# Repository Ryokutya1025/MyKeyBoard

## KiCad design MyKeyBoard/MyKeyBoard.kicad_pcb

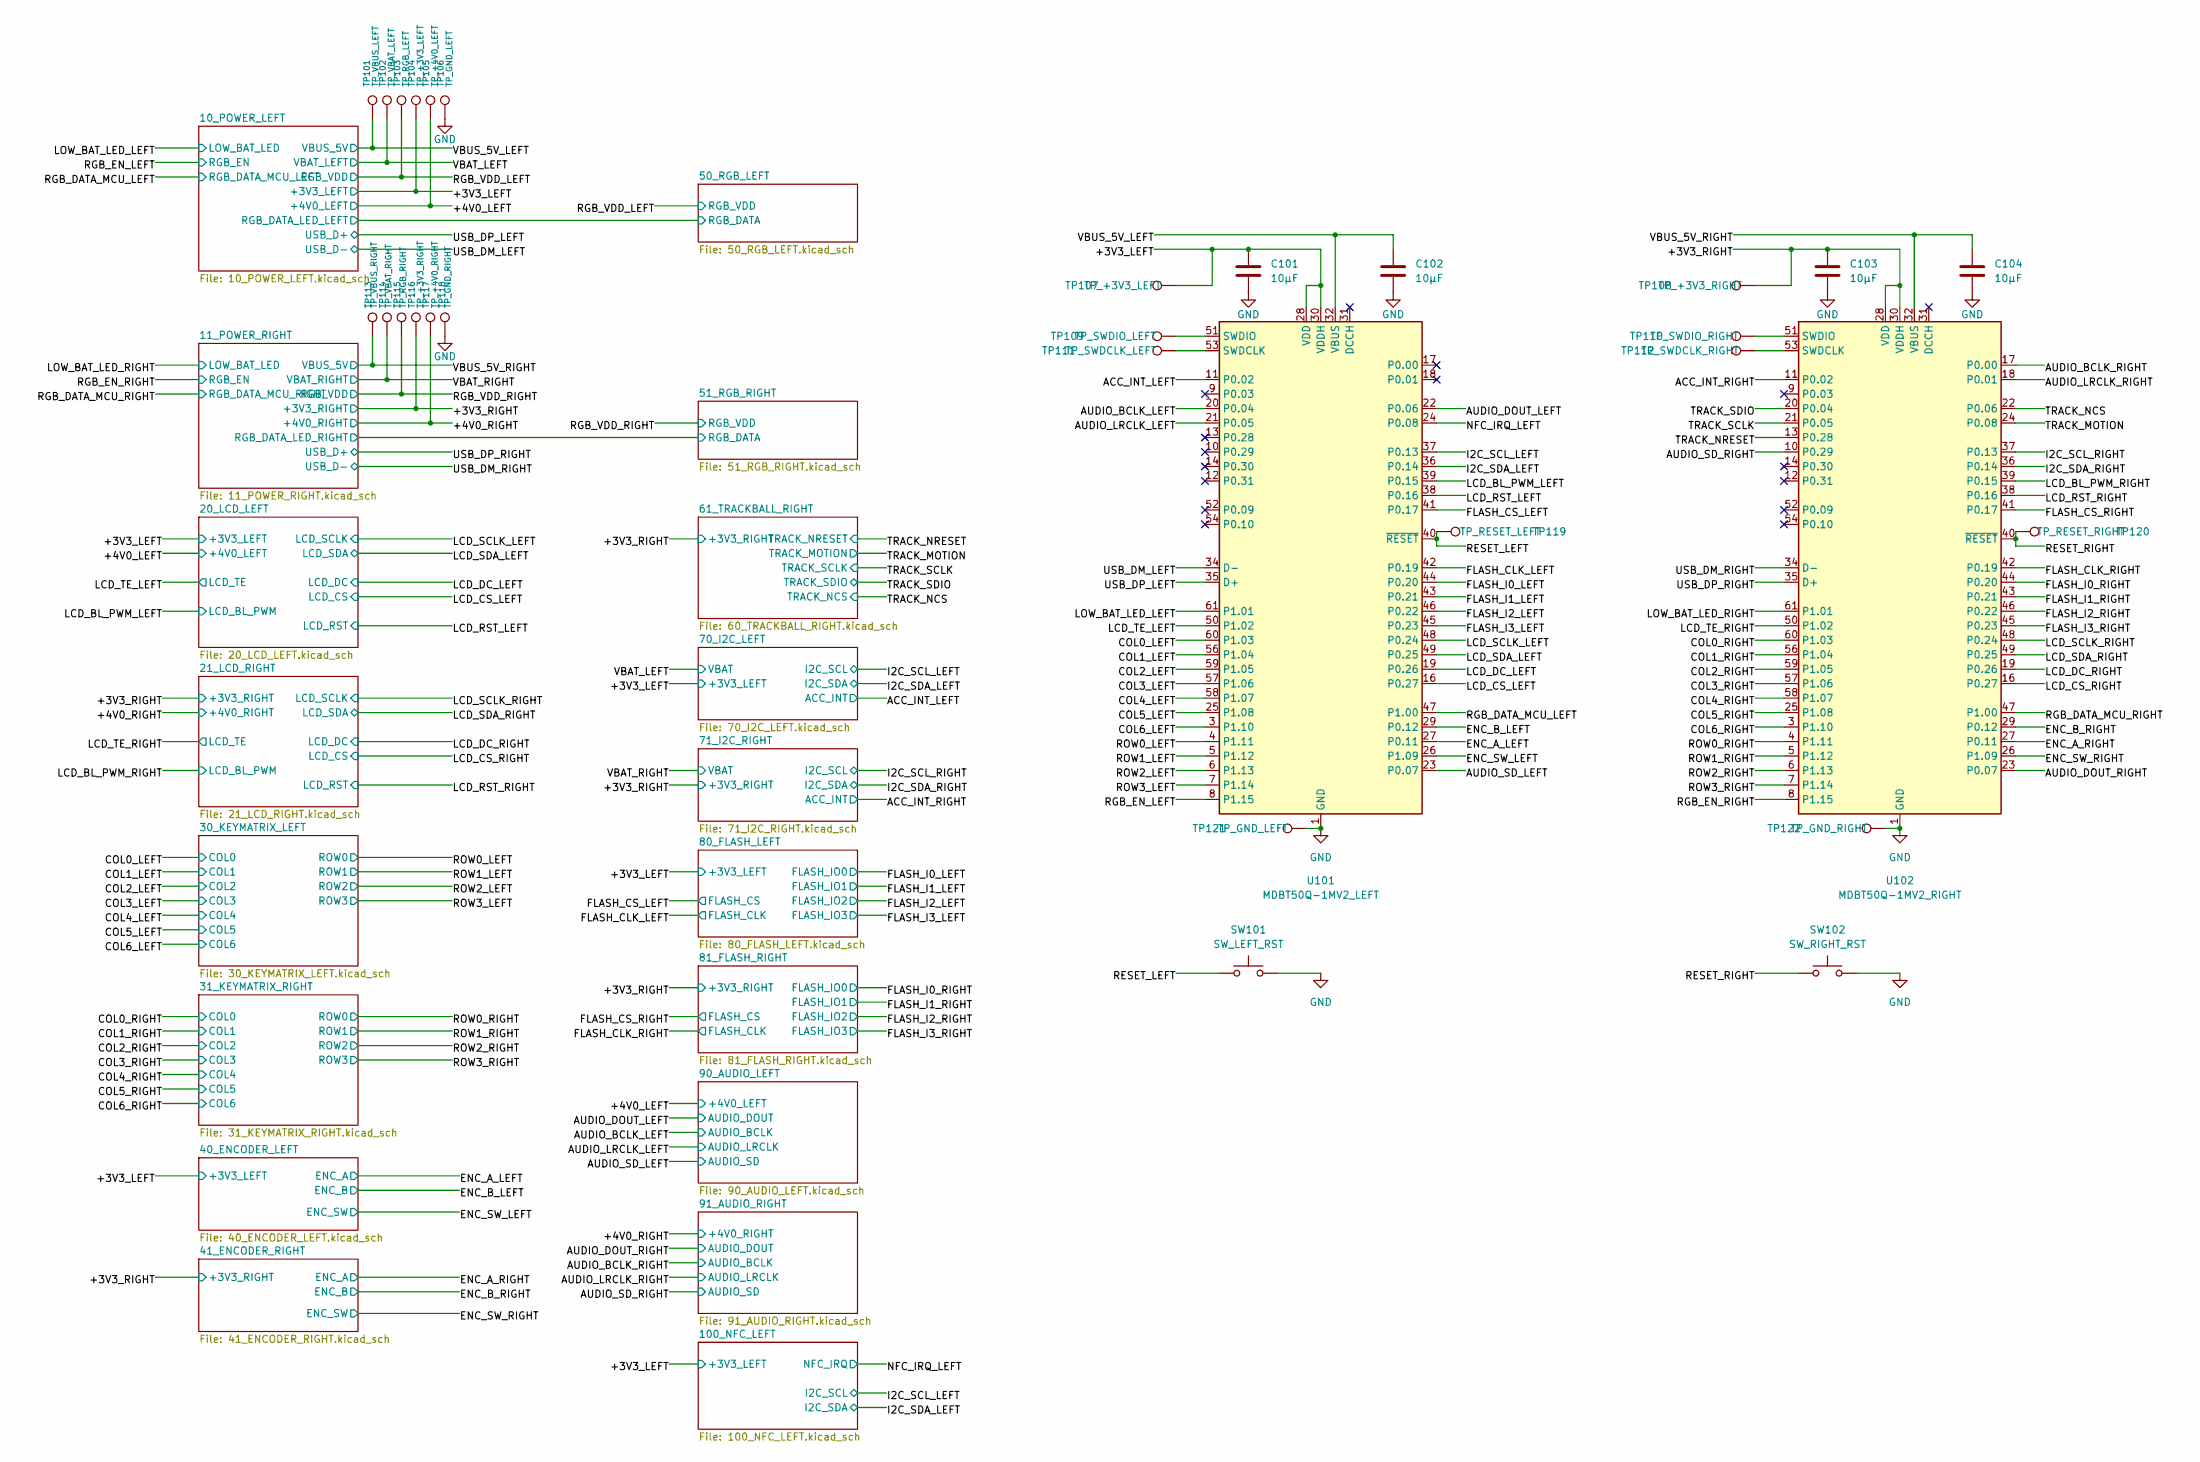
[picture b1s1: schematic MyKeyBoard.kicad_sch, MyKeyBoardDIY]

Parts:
C101, C102, C103, C104: 10µF; C_0805_2012Metric
SW101: SW_LEFT_RST; SW_SPST_B3U-1000P
SW102: SW_RIGHT_RST; SW_SPST_B3U-1000P
TP101: TP_VBUS_LEFT; TestPoint_Pad_D1.5mm
TP102: TP_VBAT_LEFT; TestPoint_Pad_D1.5mm
TP103: TP_RGB_LEFT; TestPoint_Pad_D1.5mm
TP104, TP107: TP_+3V3_LEFT; TestPoint_Pad_D1.5mm
TP105: TP_+4V0_LEFT; TestPoint_Pad_D1.5mm
TP106, TP121: TP_GND_LEFT; TestPoint_Pad_D1.5mm
TP108, TP116: TP_+3V3_RIGHT; TestPoint_Pad_D1.5mm
TP109: TP_SWDIO_LEFT; TestPoint_Pad_D1.5mm
TP110: TP_SWDIO_RIGHT; TestPoint_Pad_D1.5mm
TP111: TP_SWDCLK_LEFT; TestPoint_Pad_D1.5mm
TP112: TP_SWDCLK_RIGHT; TestPoint_Pad_D1.5mm
TP113: TP_VBUS_RIGHT; TestPoint_Pad_D1.5mm
TP114: TP_VBAT_RIGHT; TestPoint_Pad_D1.5mm
TP115: TP_RGB_RIGHT; TestPoint_Pad_D1.5mm
TP117: TP_+4V0_RIGHT; TestPoint_Pad_D1.5mm
TP118, TP122: TP_GND_RIGHT; TestPoint_Pad_D1.5mm
TP119: TP_RESET_LEFT; TestPoint_Pad_D1.5mm
TP120: TP_RESET_RIGHT; TestPoint_Pad_D1.5mm
U101: MDBT50Q-1MV2_LEFT; Raytac_MDBT50Q
U102: MDBT50Q-1MV2_RIGHT; Raytac_MDBT50Q

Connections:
/+3V3_LEFT: C101.2, TP104.1 (1_1), TP107.1 (1_1), U101.28 (VDD), U101.30 (VDDH); also elsewhere on the board
/+3V3_RIGHT: C103.1, TP108.1 (1_1), TP116.1 (1_1), U102.28 (VDD), U102.30 (VDDH); also elsewhere on the board
/+4V0_LEFT: TP105.1 (1_1); also elsewhere on the board
/+4V0_RIGHT: TP117.1 (1_1); also elsewhere on the board
/ACC_INT_LEFT: U101.11 (P0.02); also elsewhere on the board
/ACC_INT_RIGHT: U102.11 (P0.02); also elsewhere on the board
/AUDIO_BCLK_LEFT: U101.20 (P0.04); also elsewhere on the board
/AUDIO_BCLK_RIGHT: U102.17 (P0.00); also elsewhere on the board
/AUDIO_DOUT_LEFT: U101.22 (P0.06); also elsewhere on the board
/AUDIO_DOUT_RIGHT: U102.23 (P0.07); also elsewhere on the board
/AUDIO_LRCLK_LEFT: U101.21 (P0.05); also elsewhere on the board
/AUDIO_LRCLK_RIGHT: U102.18 (P0.01); also elsewhere on the board
/AUDIO_SD_LEFT: U101.23 (P0.07); also elsewhere on the board
/AUDIO_SD_RIGHT: U102.10 (P0.29); also elsewhere on the board
/COL0_LEFT: U101.60 (P1.03); also elsewhere on the board
/COL0_RIGHT: U102.60 (P1.03); also elsewhere on the board
/COL1_LEFT: U101.56 (P1.04); also elsewhere on the board
/COL1_RIGHT: U102.56 (P1.04); also elsewhere on the board
/COL2_LEFT: U101.59 (P1.05); also elsewhere on the board
/COL2_RIGHT: U102.59 (P1.05); also elsewhere on the board
/COL3_LEFT: U101.57 (P1.06); also elsewhere on the board
/COL3_RIGHT: U102.57 (P1.06); also elsewhere on the board
/COL4_LEFT: U101.58 (P1.07); also elsewhere on the board
/COL4_RIGHT: U102.58 (P1.07); also elsewhere on the board
/COL5_LEFT: U101.25 (P1.08); also elsewhere on the board
/COL5_RIGHT: U102.25 (P1.08); also elsewhere on the board
/COL6_LEFT: U101.3 (P1.10); also elsewhere on the board
/COL6_RIGHT: U102.3 (P1.10); also elsewhere on the board
/ENC_A_LEFT: U101.27 (P0.11); also elsewhere on the board
/ENC_A_RIGHT: U102.27 (P0.11); also elsewhere on the board
/ENC_B_LEFT: U101.29 (P0.12); also elsewhere on the board
/ENC_B_RIGHT: U102.29 (P0.12); also elsewhere on the board
/ENC_SW_LEFT: U101.26 (P1.09); also elsewhere on the board
/ENC_SW_RIGHT: U102.26 (P1.09); also elsewhere on the board
/FLASH_CLK_LEFT: U101.42 (P0.19); also elsewhere on the board
/FLASH_CLK_RIGHT: U102.42 (P0.19); also elsewhere on the board
/FLASH_CS_LEFT: U101.41 (P0.17); also elsewhere on the board
/FLASH_CS_RIGHT: U102.41 (P0.17); also elsewhere on the board
/FLASH_I0_LEFT: U101.44 (P0.20); also elsewhere on the board
/FLASH_I0_RIGHT: U102.44 (P0.20); also elsewhere on the board
/FLASH_I1_LEFT: U101.43 (P0.21); also elsewhere on the board
/FLASH_I1_RIGHT: U102.43 (P0.21); also elsewhere on the board
/FLASH_I2_LEFT: U101.46 (P0.22); also elsewhere on the board
/FLASH_I2_RIGHT: U102.46 (P0.22); also elsewhere on the board
/FLASH_I3_LEFT: U101.45 (P0.23); also elsewhere on the board
/FLASH_I3_RIGHT: U102.45 (P0.23); also elsewhere on the board
/I2C_SCL_LEFT: U101.37 (P0.13); also elsewhere on the board
/I2C_SCL_RIGHT: U102.37 (P0.13); also elsewhere on the board
/I2C_SDA_LEFT: U101.36 (P0.14); also elsewhere on the board
/I2C_SDA_RIGHT: U102.36 (P0.14); also elsewhere on the board
/LCD_BL_PWM_LEFT: U101.39 (P0.15); also elsewhere on the board
/LCD_BL_PWM_RIGHT: U102.39 (P0.15); also elsewhere on the board
/LCD_CS_LEFT: U101.16 (P0.27); also elsewhere on the board
/LCD_CS_RIGHT: U102.16 (P0.27); also elsewhere on the board
/LCD_DC_LEFT: U101.19 (P0.26); also elsewhere on the board
/LCD_DC_RIGHT: U102.19 (P0.26); also elsewhere on the board
/LCD_RST_LEFT: U101.38 (P0.16); also elsewhere on the board
/LCD_RST_RIGHT: U102.38 (P0.16); also elsewhere on the board
/LCD_SCLK_LEFT: U101.48 (P0.24); also elsewhere on the board
/LCD_SCLK_RIGHT: U102.48 (P0.24); also elsewhere on the board
/LCD_SDA_LEFT: U101.49 (P0.25); also elsewhere on the board
/LCD_SDA_RIGHT: U102.49 (P0.25); also elsewhere on the board
/LCD_TE_LEFT: U101.50 (P1.02); also elsewhere on the board
/LCD_TE_RIGHT: U102.50 (P1.02); also elsewhere on the board
/LOW_BAT_LED_LEFT: U101.61 (P1.01); also elsewhere on the board
/LOW_BAT_LED_RIGHT: U102.61 (P1.01); also elsewhere on the board
/NFC_IRQ_LEFT: U101.24 (P0.08); also elsewhere on the board
/RESET_LEFT: SW101.1, TP119.1 (1_1), U101.40 (~RESET)
/RESET_RIGHT: SW102.1, TP120.1 (1_1), U102.40 (~RESET)
/RGB_DATA_MCU_LEFT: U101.47 (P1.00); also elsewhere on the board
/RGB_DATA_MCU_RIGHT: U102.47 (P1.00); also elsewhere on the board
/RGB_EN_LEFT: U101.8 (P1.15); also elsewhere on the board
/RGB_EN_RIGHT: U102.8 (P1.15); also elsewhere on the board
/RGB_VDD_LEFT: TP103.1 (1_1); also elsewhere on the board
/RGB_VDD_RIGHT: TP115.1 (1_1); also elsewhere on the board
/ROW0_LEFT: U101.4 (P1.11); also elsewhere on the board
/ROW0_RIGHT: U102.4 (P1.11); also elsewhere on the board
/ROW1_LEFT: U101.5 (P1.12); also elsewhere on the board
/ROW1_RIGHT: U102.5 (P1.12); also elsewhere on the board
/ROW2_LEFT: U101.6 (P1.13); also elsewhere on the board
/ROW2_RIGHT: U102.6 (P1.13); also elsewhere on the board
/ROW3_LEFT: U101.7 (P1.14); also elsewhere on the board
/ROW3_RIGHT: U102.7 (P1.14); also elsewhere on the board
/TRACK_MOTION: U102.24 (P0.08); also elsewhere on the board
/TRACK_NCS: U102.22 (P0.06); also elsewhere on the board
/TRACK_NRESET: U102.13 (P0.28); also elsewhere on the board
/TRACK_SCLK: U102.21 (P0.05); also elsewhere on the board
/TRACK_SDIO: U102.20 (P0.04); also elsewhere on the board
/USB_DM_LEFT: U101.34 (D-); also elsewhere on the board
/USB_DM_RIGHT: U102.34 (D-); also elsewhere on the board
/USB_DP_LEFT: U101.35 (D+); also elsewhere on the board
/USB_DP_RIGHT: U102.35 (D+); also elsewhere on the board
/VBAT_LEFT: TP102.1 (1_1); also elsewhere on the board
/VBAT_RIGHT: TP114.1 (1_1); also elsewhere on the board
/VBUS_5V_LEFT: C102.2, TP101.1 (1_1), U101.32 (VBUS); also elsewhere on the board
/VBUS_5V_RIGHT: C104.1, TP113.1 (1_1), U102.32 (VBUS); also elsewhere on the board
GND: C101.1, C102.1, C103.2, C104.2, SW101.2, SW102.2, TP106.1 (1_1), TP118.1 (1_1), TP121.1 (1_1), TP122.1 (1_1), U101.1 (GND), U101.2 (GND), U101.15 (GND), U101.33 (GND), U101.55 (GND), U102.1 (GND), U102.2 (GND), U102.15 (GND), U102.33 (GND), U102.55 (GND); also elsewhere on the board
unnamed: TP111.1 (1_1), U101.53 (SWDCLK)
unnamed: TP109.1 (1_1), U101.51 (SWDIO)
unnamed: TP112.1 (1_1), U102.53 (SWDCLK)
unnamed: TP110.1 (1_1), U102.51 (SWDIO)

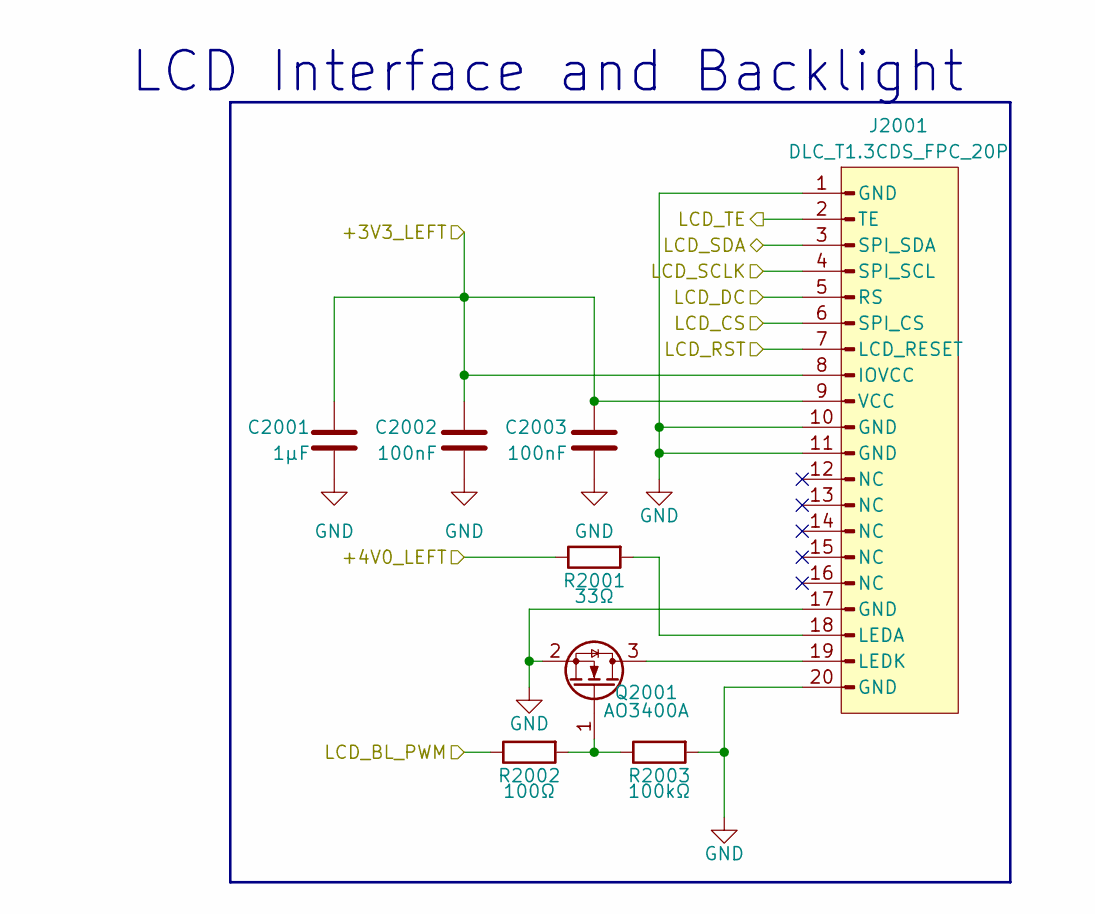
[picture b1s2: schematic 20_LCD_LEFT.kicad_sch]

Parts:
C2001: 1µF; C_0603_1608Metric
C2002, C2003: 100nF; C_0603_1608Metric
J2001: DLC_T1.3CDS_FPC_20P
Q2001: AO3400A; SOT-23
R2001: 33Ω; R_0603_1608Metric
R2002: 100Ω; R_0603_1608Metric
R2003: 100kΩ; R_0603_1608Metric

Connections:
/+3V3_LEFT: C2001.1, C2002.1, C2003.1, J2001.8 (IOVCC), J2001.9 (VCC); also elsewhere on the board
/+4V0_LEFT: R2001.1; also elsewhere on the board
/LCD_BL_PWM_LEFT: R2002.1; also elsewhere on the board
/LCD_CS_LEFT: J2001.6 (SPI_CS); also elsewhere on the board
/LCD_DC_LEFT: J2001.5 (RS); also elsewhere on the board
/LCD_RST_LEFT: J2001.7 (LCD_RESET); also elsewhere on the board
/LCD_SCLK_LEFT: J2001.4 (SPI_SCL); also elsewhere on the board
/LCD_SDA_LEFT: J2001.3 (SPI_SDA); also elsewhere on the board
/LCD_TE_LEFT: J2001.2 (TE); also elsewhere on the board
GND: C2001.2, C2002.2, C2003.2, J2001.1 (GND), J2001.10 (GND), J2001.11 (GND), J2001.17 (GND), J2001.20 (GND), Q2001.2 (S), R2003.2; also elsewhere on the board
unnamed: J2001.18 (LEDA), R2001.2
unnamed: J2001.19 (LEDK), Q2001.3 (D)
unnamed: Q2001.1 (G), R2002.2, R2003.1

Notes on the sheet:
LCD Interface and Backlight

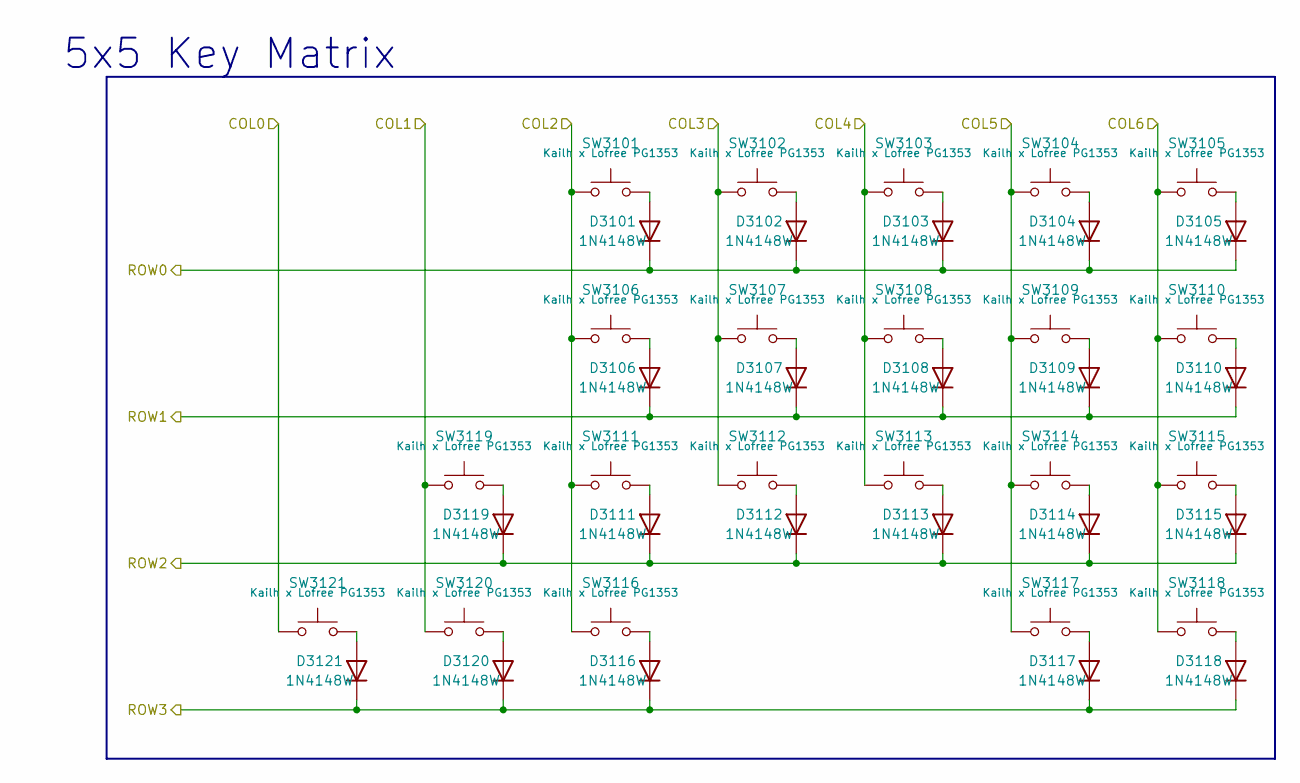
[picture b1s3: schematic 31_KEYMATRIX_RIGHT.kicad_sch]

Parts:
D3101, D3102, D3103, D3104, D3105, D3106, D3107, D3108, D3109, D3110, D3111, D3112, D3113, D3114, D3115, D3116, D3117, D3118, D3119, D3120, D3121: 1N4148W; D_SOD-123
SW3101, SW3102, SW3103, SW3104, SW3105, SW3106, SW3107, SW3108, SW3109, SW3110, SW3111, SW3112, SW3113, SW3114, SW3115, SW3116, SW3117, SW3118, SW3119, SW3120, SW3121: Kailh x Lofree PG1353; Kailh-PG1353-Hotswap-1U

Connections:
/COL0_RIGHT: SW3121.1; also elsewhere on the board
/COL1_RIGHT: SW3119.1, SW3120.1; also elsewhere on the board
/COL2_RIGHT: SW3101.1, SW3106.1, SW3111.1, SW3116.1; also elsewhere on the board
/COL3_RIGHT: SW3102.1, SW3107.1, SW3112.1; also elsewhere on the board
/COL4_RIGHT: SW3103.1, SW3108.1, SW3113.1; also elsewhere on the board
/COL5_RIGHT: SW3104.1, SW3109.1, SW3114.1, SW3117.1; also elsewhere on the board
/COL6_RIGHT: SW3105.1, SW3110.1, SW3115.1, SW3118.1; also elsewhere on the board
/ROW0_RIGHT: D3101.1 (K), D3102.1 (K), D3103.1 (K), D3104.1 (K), D3105.1 (K); also elsewhere on the board
/ROW1_RIGHT: D3106.1 (K), D3107.1 (K), D3108.1 (K), D3109.1 (K), D3110.1 (K); also elsewhere on the board
/ROW2_RIGHT: D3111.1 (K), D3112.1 (K), D3113.1 (K), D3114.1 (K), D3115.1 (K), D3119.1 (K); also elsewhere on the board
/ROW3_RIGHT: D3116.1 (K), D3117.1 (K), D3118.1 (K), D3120.1 (K), D3121.1 (K); also elsewhere on the board
unnamed: D3101.2 (A), SW3101.2
unnamed: D3102.2 (A), SW3102.2
unnamed: D3103.2 (A), SW3103.2
unnamed: D3104.2 (A), SW3104.2
unnamed: D3105.2 (A), SW3105.2
unnamed: D3106.2 (A), SW3106.2
unnamed: D3107.2 (A), SW3107.2
unnamed: D3108.2 (A), SW3108.2
unnamed: D3109.2 (A), SW3109.2
unnamed: D3110.2 (A), SW3110.2
unnamed: D3111.2 (A), SW3111.2
unnamed: D3112.2 (A), SW3112.2
unnamed: D3113.2 (A), SW3113.2
unnamed: D3114.2 (A), SW3114.2
unnamed: D3115.2 (A), SW3115.2
unnamed: D3116.2 (A), SW3116.2
unnamed: D3117.2 (A), SW3117.2
unnamed: D3118.2 (A), SW3118.2
unnamed: D3119.2 (A), SW3119.2
unnamed: D3120.2 (A), SW3120.2
unnamed: D3121.2 (A), SW3121.2

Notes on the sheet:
5x5 Key Matrix

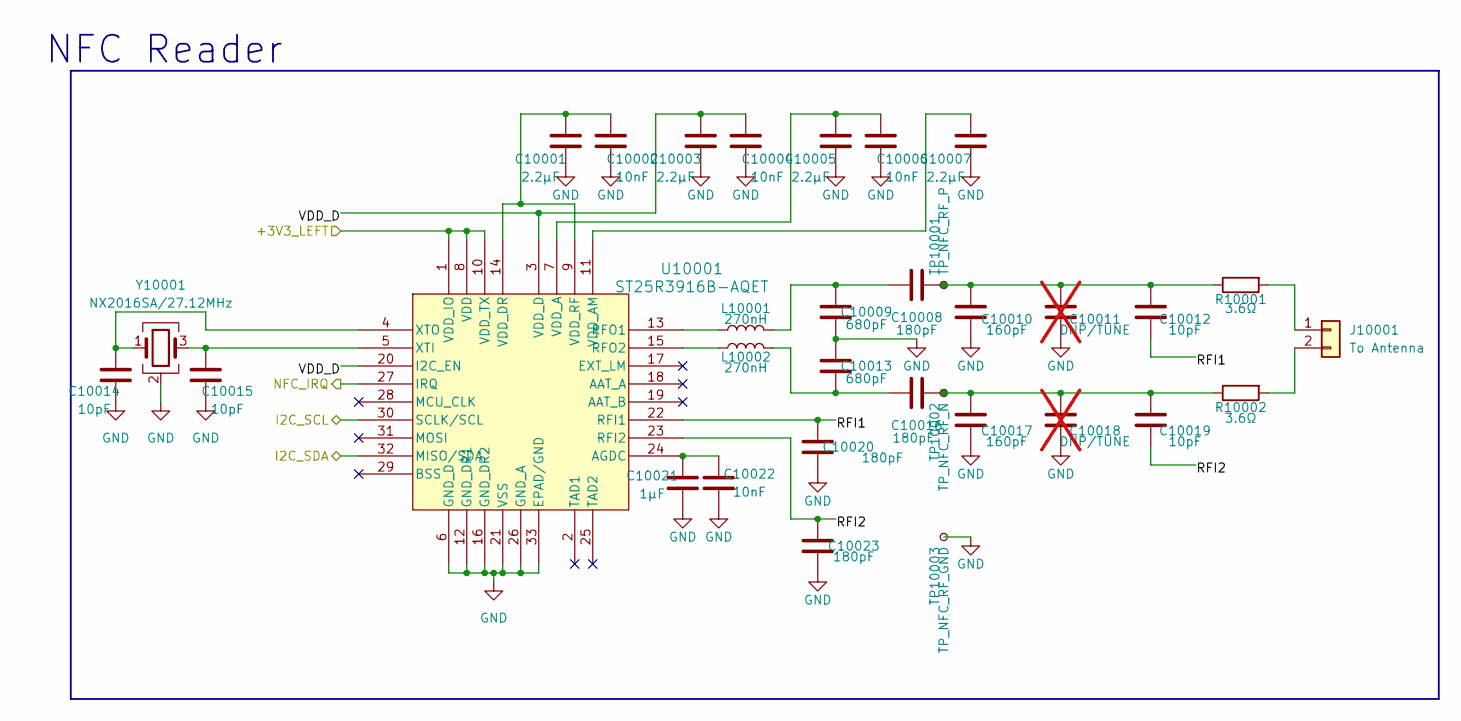
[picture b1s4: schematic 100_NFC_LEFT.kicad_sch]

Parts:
C10001, C10003, C10005, C10007: 2.2µF; C_0805_2012Metric
C10002, C10004, C10006, C10022: 10nF; C_0603_1608Metric
C10008, C10016, C10020, C10023: 180pF; C_0603_1608Metric
C10009, C10013: 680pF; C_0603_1608Metric
C10010, C10017: 160pF; C_0603_1608Metric
C10011, C10018: DNP/TUNE; C_0603_1608Metric; not fitted
C10012, C10014, C10015, C10019: 10pF; C_0603_1608Metric
C10021: 1µF; C_0603_1608Metric
J10001: To Antenna; JST_SH_SM02B-SRSS-TB_1x02-1MP_P1.00mm_Horizontal
L10001, L10002: 270nH; L_0603_1608Metric
R10001, R10002: 3.6Ω; R_0603_1608Metric
TP10001: TP_NFC_RF_P; TestPoint_Pad_D1.0mm
TP10002: TP_NFC_RF_N; TestPoint_Pad_D1.0mm
TP10003: TP_NFC_RF_GND; TestPoint_Pad_D1.5mm
U10001: ST25R3916B-AQET; UFQFPN32-5x5x0p55_STM
Y10001: NX2016SA/27.12MHz; Crystal_SMD_2016-4Pin_2.0x1.6mm

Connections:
/100_NFC_LEFT/RFI1: C10012.1, C10020.1, U10001.22 (RFI1)
/100_NFC_LEFT/RFI2: C10019.1, C10023.1, U10001.23 (RFI2)
/100_NFC_LEFT/VDD_D: C10003.1, C10004.1, U10001.3 (VDD_D), U10001.20 (I2C_EN)
/+3V3_LEFT: U10001.1 (VDD_IO), U10001.8 (VDD), U10001.10 (VDD_TX); also elsewhere on the board
/I2C_SCL_LEFT: U10001.30 (SCLK/SCL); also elsewhere on the board
/I2C_SDA_LEFT: U10001.32 (MISO/SDA); also elsewhere on the board
/NFC_IRQ_LEFT: U10001.27 (IRQ); also elsewhere on the board
GND: C10001.2, C10002.2, C10003.2, C10004.2, C10005.2, C10006.2, C10007.2, C10009.2, C10010.1, C10011.1, C10013.1, C10014.2, C10015.2, C10017.1, C10018.1, C10020.2, C10021.2, C10022.2, C10023.2, TP10003.1 (1_1), U10001.6 (GND_D), U10001.12 (GND_DR1), U10001.16 (GND_DR2), U10001.21 (VSS), U10001.26 (GND_A), U10001.33 (EPAD/GND), Y10001.2 (G), Y10001.4 (G); also elsewhere on the board
unnamed: C10008.1, C10009.1, L10001.2
unnamed: C10008.2, C10010.2, C10011.2, C10012.2, R10001.1, TP10001.1 (1_1)
unnamed: C10013.2, C10016.1, L10002.1
unnamed: C10016.2, C10017.2, C10018.2, C10019.2, R10002.1, TP10002.1 (1_1)
unnamed: J10001.1, R10001.2
unnamed: J10001.2, R10002.2
unnamed: C10021.1, C10022.1, U10001.24 (AGDC)
unnamed: L10001.1, U10001.13 (RFO1)
unnamed: L10002.2, U10001.15 (RFO2)
unnamed: C10005.1, C10006.1, U10001.7 (VDD_A)
unnamed: C10007.1, U10001.11 (VDD_AM)
unnamed: C10001.1, C10002.1, U10001.9 (VDD_RF), U10001.14 (VDD_DR)
unnamed: C10015.1, U10001.5 (XTI), Y10001.3
unnamed: C10014.1, U10001.4 (XTO), Y10001.1

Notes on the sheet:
NFC Reader

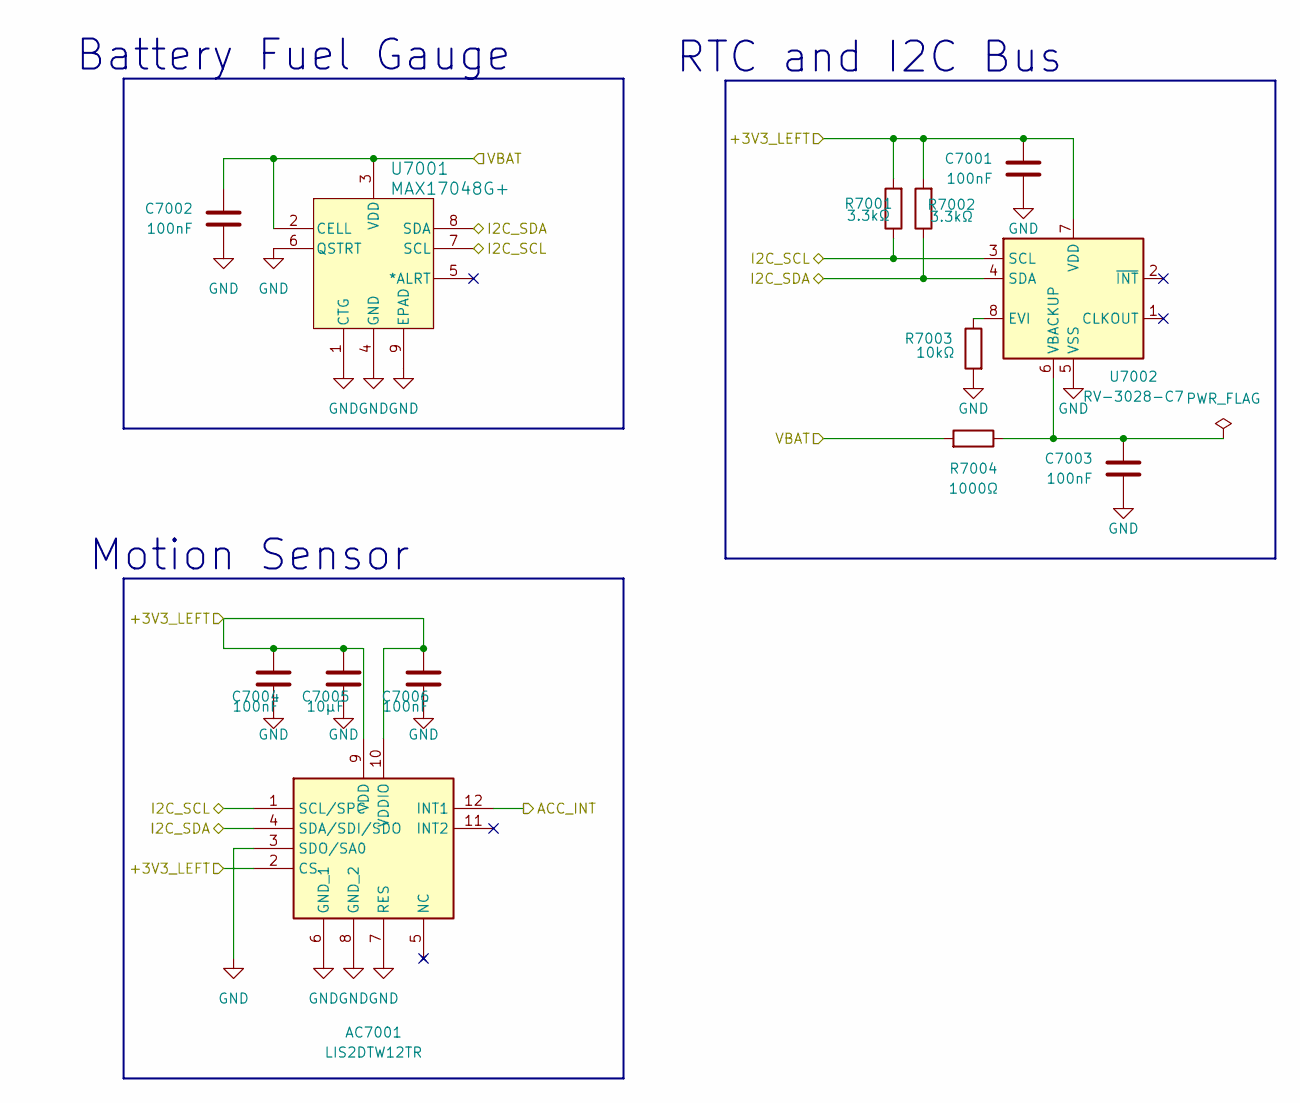
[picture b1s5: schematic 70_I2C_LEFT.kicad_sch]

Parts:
AC7001: LIS2DTW12TR; LGA-12_2x2mm_P0.5mm; Mouser Part Number 511-LIS2DTW12TR
C7001, C7002, C7003, C7004, C7006: 100nF; C_0603_1608Metric
C7005: 10µF; C_0805_2012Metric
R7001, R7002: 3.3kΩ; R_0603_1608Metric
R7003: 10kΩ; R_0603_1608Metric
R7004: 1000Ω; R_0603_1608Metric
U7001: MAX17048G+
U7002: RV-3028-C7

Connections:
/+3V3_LEFT: AC7001.2 (CS), AC7001.9 (VDD), AC7001.10 (VDDIO), C7001.1, C7004.1, C7005.1, C7006.1, R7001.2, R7002.2, U7002.7 (VDD); also elsewhere on the board
/ACC_INT_LEFT: AC7001.12 (INT1); also elsewhere on the board
/I2C_SCL_LEFT: AC7001.1 (SCL/SPC), R7001.1, U7001.7 (SCL), U7002.3 (SCL); also elsewhere on the board
/I2C_SDA_LEFT: AC7001.4 (SDA/SDI/SDO), R7002.1, U7001.8 (SDA), U7002.4 (SDA); also elsewhere on the board
/VBAT_LEFT: C7002.1, R7004.2, U7001.2 (CELL), U7001.3 (VDD); also elsewhere on the board
GND: AC7001.3 (SDO/SA0), AC7001.6 (GND_1), AC7001.7 (RES), AC7001.8 (GND_2), C7001.2, C7002.2, C7003.2, C7004.2, C7005.2, C7006.2, R7003.2, U7001.1 (CTG), U7001.4 (GND), U7001.6 (QSTRT), U7001.9 (EPAD), U7002.5 (VSS); also elsewhere on the board
unnamed: R7003.1, U7002.8 (EVI)
unnamed: C7003.1, R7004.1, U7002.6 (VBACKUP)

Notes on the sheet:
Battery Fuel Gauge
RTC and I2C Bus
Motion Sensor

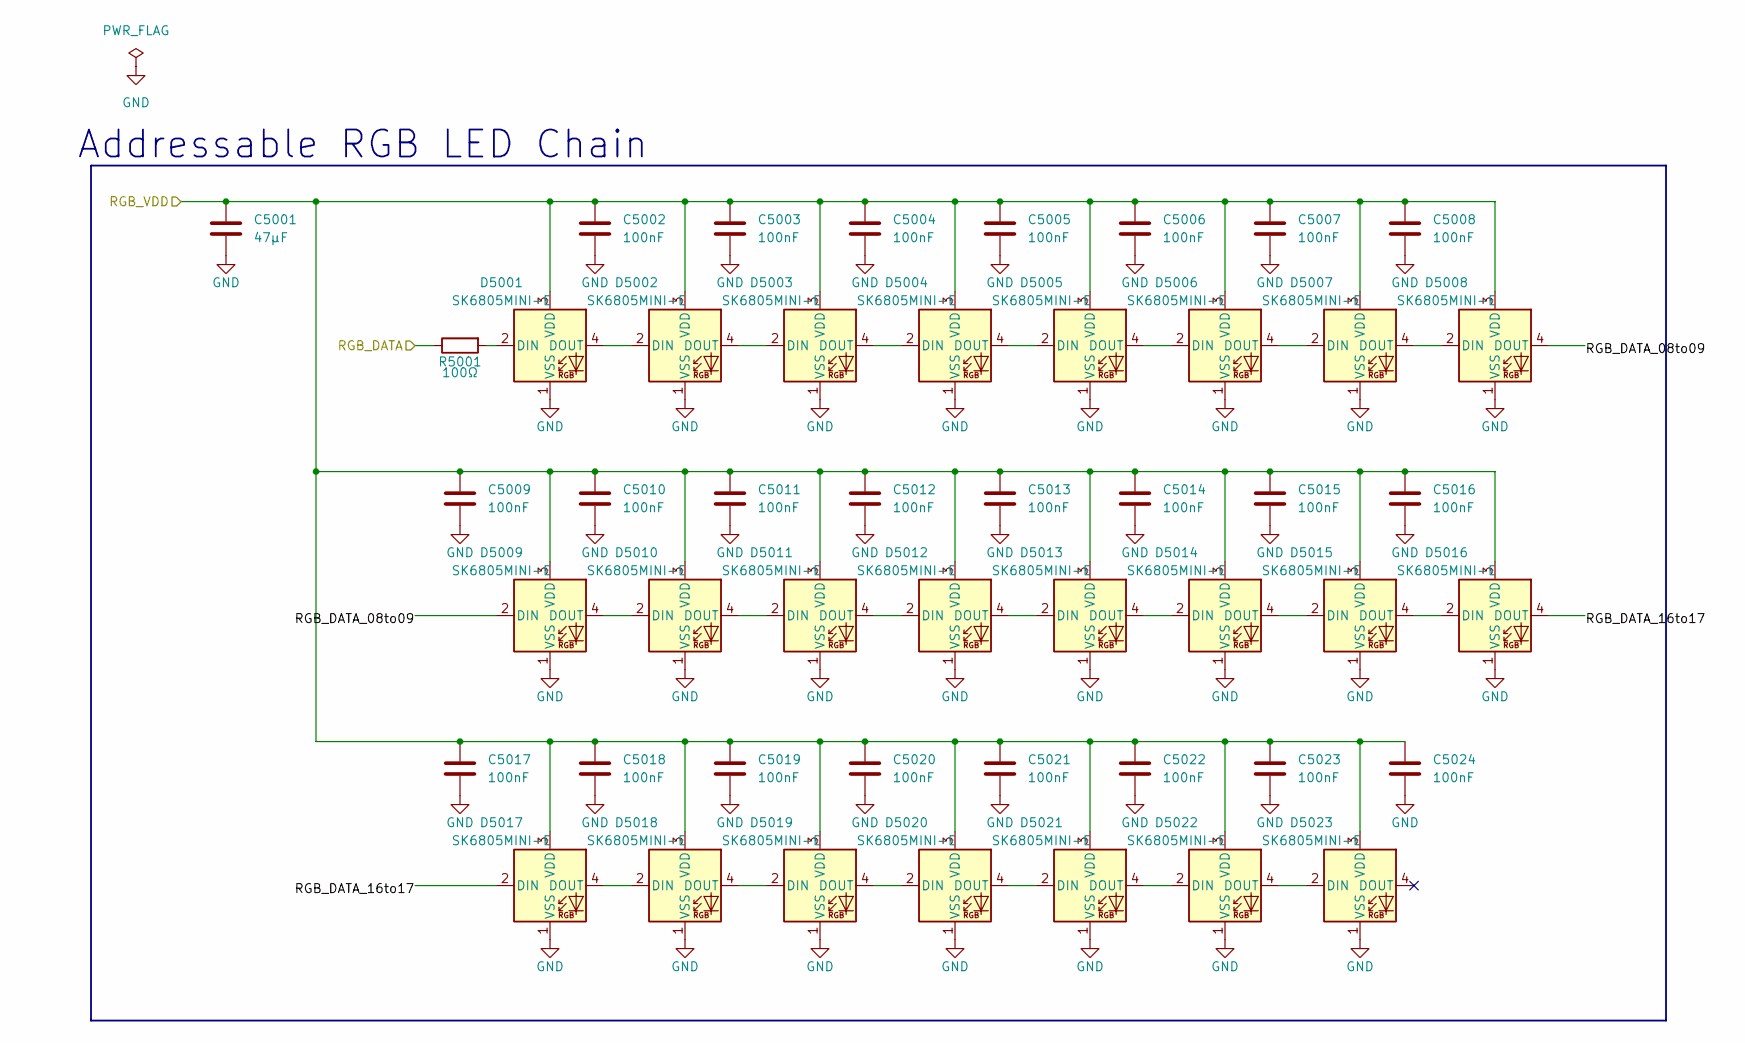
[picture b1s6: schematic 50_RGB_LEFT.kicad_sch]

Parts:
C5001: 47µF; C_1210_3225Metric
C5002, C5003, C5004, C5005, C5006, C5007, C5008, C5009, C5010, C5011, C5012, C5013, C5014, C5015, C5016, C5017, C5018, C5019, C5020, C5021, C5022, C5023, C5024: 100nF; C_0603_1608Metric
D5001, D5002, D5003, D5004, D5005, D5006, D5007, D5008, D5009, D5010, D5011, D5012, D5013, D5014, D5015, D5016, D5017, D5018, D5019, D5020, D5021, D5022, D5023: SK6805MINI-E
R5001: 100Ω; R_0603_1608Metric

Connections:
/10_POWER_LEFT/RGB_DATA_LED_LEFT: R5001.1; also elsewhere on the board
/50_RGB_LEFT/RGB_DATA_08to09: D5008.4 (DOUT), D5009.2 (DIN)
/50_RGB_LEFT/RGB_DATA_16to17: D5016.4 (DOUT), D5017.2 (DIN)
/RGB_VDD_LEFT: C5001.1, C5002.1, C5003.1, C5004.1, C5005.1, C5006.1, C5007.1, C5008.1, C5009.1, C5010.1, C5011.1, C5012.1, C5013.1, C5014.1, C5015.1, C5016.1, C5017.1, C5018.1, C5019.1, C5020.1, C5021.1, C5022.1, C5023.1, C5024.1, D5001.3 (VDD), D5002.3 (VDD), D5003.3 (VDD), D5004.3 (VDD), D5005.3 (VDD), D5006.3 (VDD), D5007.3 (VDD), D5008.3 (VDD), D5009.3 (VDD), D5010.3 (VDD), D5011.3 (VDD), D5012.3 (VDD), D5013.3 (VDD), D5014.3 (VDD), D5015.3 (VDD), D5016.3 (VDD), D5017.3 (VDD), D5018.3 (VDD), D5019.3 (VDD), D5020.3 (VDD), D5021.3 (VDD), D5022.3 (VDD), D5023.3 (VDD); also elsewhere on the board
GND: C5001.2, C5002.2, C5003.2, C5004.2, C5005.2, C5006.2, C5007.2, C5008.2, C5009.2, C5010.2, C5011.2, C5012.2, C5013.2, C5014.2, C5015.2, C5016.2, C5017.2, C5018.2, C5019.2, C5020.2, C5021.2, C5022.2, C5023.2, C5024.2, D5001.1 (VSS), D5002.1 (VSS), D5003.1 (VSS), D5004.1 (VSS), D5005.1 (VSS), D5006.1 (VSS), D5007.1 (VSS), D5008.1 (VSS), D5009.1 (VSS), D5010.1 (VSS), D5011.1 (VSS), D5012.1 (VSS), D5013.1 (VSS), D5014.1 (VSS), D5015.1 (VSS), D5016.1 (VSS), D5017.1 (VSS), D5018.1 (VSS), D5019.1 (VSS), D5020.1 (VSS), D5021.1 (VSS), D5022.1 (VSS), D5023.1 (VSS); also elsewhere on the board
unnamed: D5001.2 (DIN), R5001.2
unnamed: D5001.4 (DOUT), D5002.2 (DIN)
unnamed: D5002.4 (DOUT), D5003.2 (DIN)
unnamed: D5003.4 (DOUT), D5004.2 (DIN)
unnamed: D5004.4 (DOUT), D5005.2 (DIN)
unnamed: D5005.4 (DOUT), D5006.2 (DIN)
unnamed: D5006.4 (DOUT), D5007.2 (DIN)
unnamed: D5007.4 (DOUT), D5008.2 (DIN)
unnamed: D5009.4 (DOUT), D5010.2 (DIN)
unnamed: D5010.4 (DOUT), D5011.2 (DIN)
unnamed: D5011.4 (DOUT), D5012.2 (DIN)
unnamed: D5012.4 (DOUT), D5013.2 (DIN)
unnamed: D5013.4 (DOUT), D5014.2 (DIN)
unnamed: D5014.4 (DOUT), D5015.2 (DIN)
unnamed: D5015.4 (DOUT), D5016.2 (DIN)
unnamed: D5017.4 (DOUT), D5018.2 (DIN)
unnamed: D5018.4 (DOUT), D5019.2 (DIN)
unnamed: D5019.4 (DOUT), D5020.2 (DIN)
unnamed: D5020.4 (DOUT), D5021.2 (DIN)
unnamed: D5021.4 (DOUT), D5022.2 (DIN)
unnamed: D5022.4 (DOUT), D5023.2 (DIN)

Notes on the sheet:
Addressable RGB LED Chain

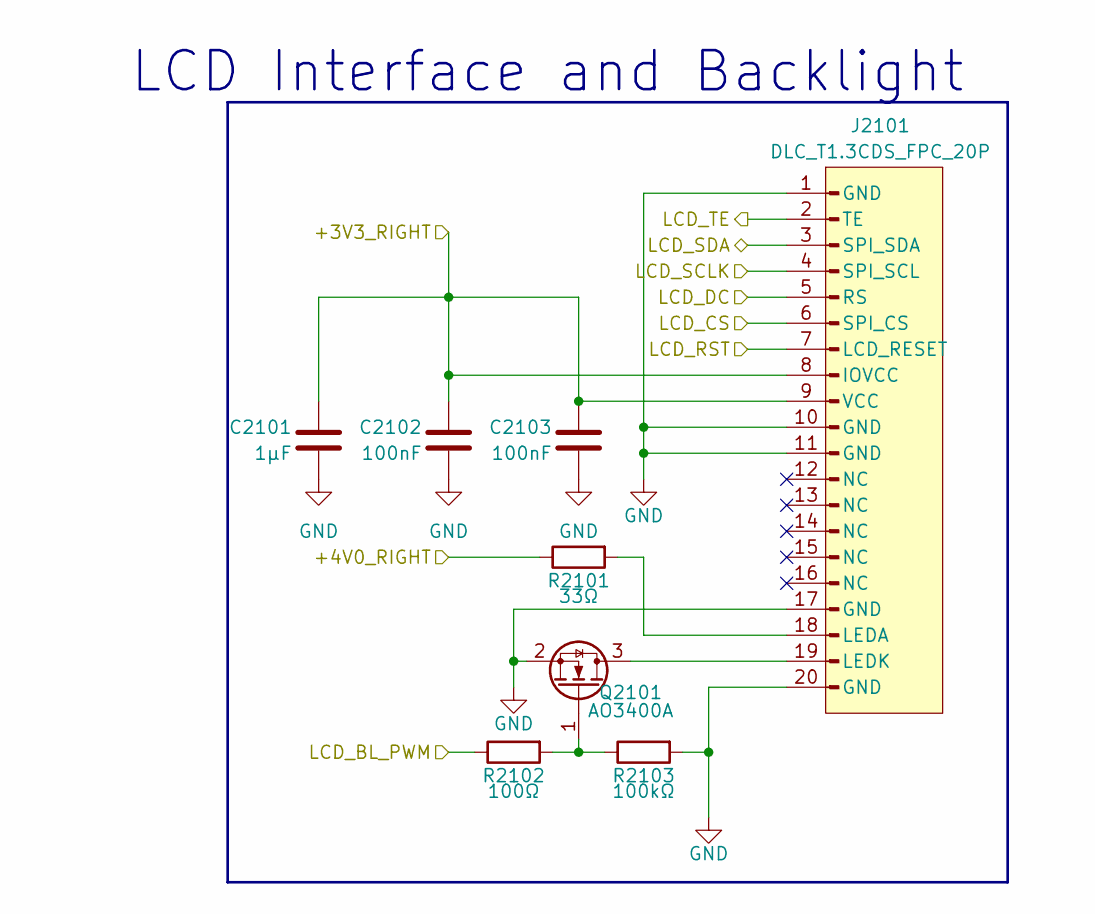
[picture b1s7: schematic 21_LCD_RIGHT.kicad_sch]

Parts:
C2101: 1µF; C_0603_1608Metric
C2102, C2103: 100nF; C_0603_1608Metric
J2101: DLC_T1.3CDS_FPC_20P
Q2101: AO3400A; SOT-23
R2101: 33Ω; R_0603_1608Metric
R2102: 100Ω; R_0603_1608Metric
R2103: 100kΩ; R_0603_1608Metric

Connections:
/+3V3_RIGHT: C2101.1, C2102.1, C2103.1, J2101.8 (IOVCC), J2101.9 (VCC); also elsewhere on the board
/+4V0_RIGHT: R2101.1; also elsewhere on the board
/LCD_BL_PWM_RIGHT: R2102.1; also elsewhere on the board
/LCD_CS_RIGHT: J2101.6 (SPI_CS); also elsewhere on the board
/LCD_DC_RIGHT: J2101.5 (RS); also elsewhere on the board
/LCD_RST_RIGHT: J2101.7 (LCD_RESET); also elsewhere on the board
/LCD_SCLK_RIGHT: J2101.4 (SPI_SCL); also elsewhere on the board
/LCD_SDA_RIGHT: J2101.3 (SPI_SDA); also elsewhere on the board
/LCD_TE_RIGHT: J2101.2 (TE); also elsewhere on the board
GND: C2101.2, C2102.2, C2103.2, J2101.1 (GND), J2101.10 (GND), J2101.11 (GND), J2101.17 (GND), J2101.20 (GND), Q2101.2 (S), R2103.2; also elsewhere on the board
unnamed: J2101.18 (LEDA), R2101.2
unnamed: J2101.19 (LEDK), Q2101.3 (D)
unnamed: Q2101.1 (G), R2102.2, R2103.1

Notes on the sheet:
LCD Interface and Backlight

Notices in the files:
parts and their libraries:
License: Apache-2.0
